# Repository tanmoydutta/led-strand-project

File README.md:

# Autonoe
An RGB and Neopixel LED controller board powered by ESP32-C3

The module has option for unified 5V supply for LEDs and the MCU LDO and can provide support for higher voltages via the dedicated barrel jack socket. Separate 5V power then can be supplied via the USB-C connector -

A small solder bridge unifies the circuit power for 5V power operations and for higher current feed via the barrel jack socket-

Dual LED interface for RGB and Addressable LEDs - 

This is an OSHWA certified hardware - 
<p align="center">
  
</p>

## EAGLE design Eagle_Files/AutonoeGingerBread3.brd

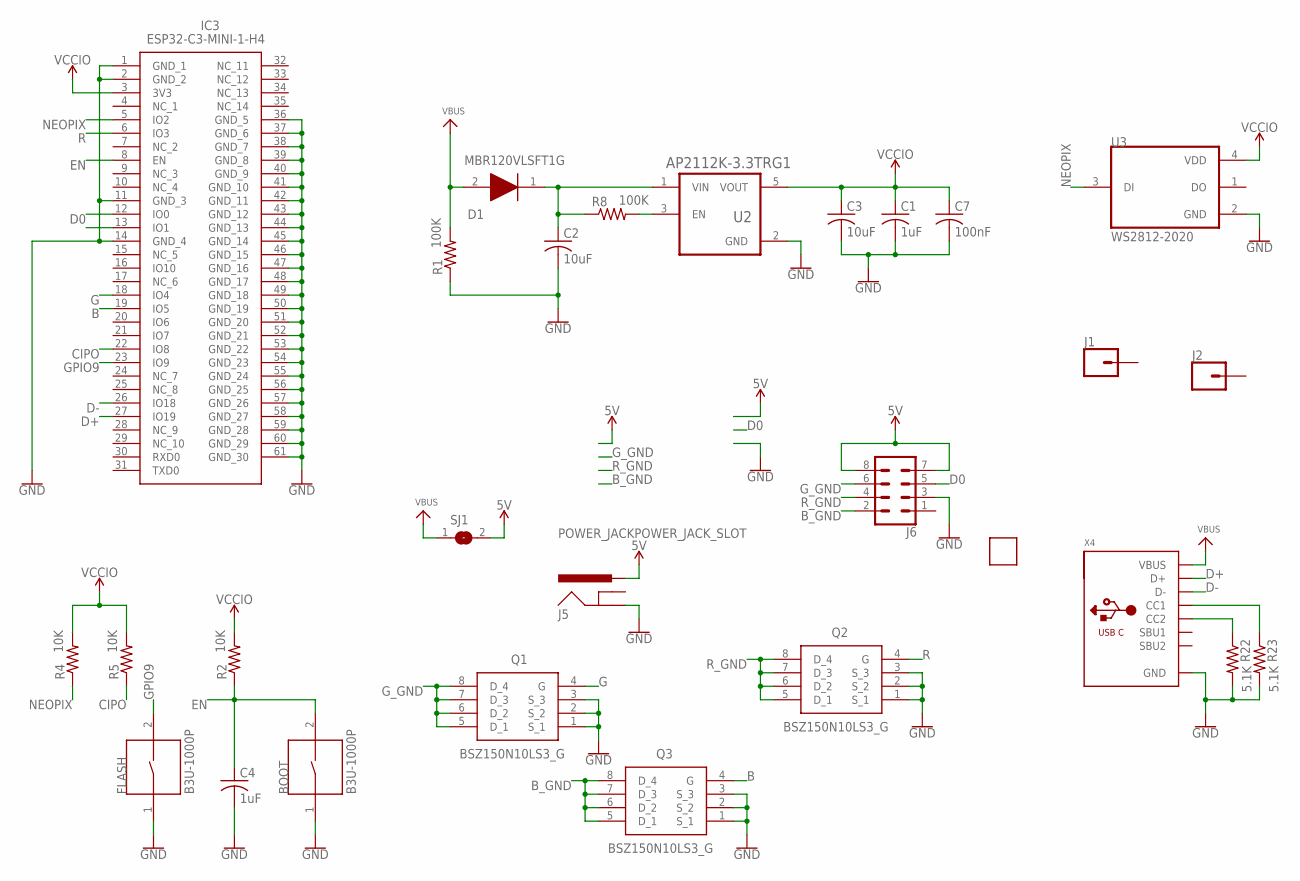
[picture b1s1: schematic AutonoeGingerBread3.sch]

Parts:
BOOT: B3U-1000P; SW_B3U-1000P
C1, C4: 1uF; C0402
C2, C3: 10uF; C0402
C7: 100nF; C0402
D1: MBR120VLSFT1G; SODFL3616X98N
FLASH: B3U-1000P; SW_B3U-1000P
IC3: ESP32-C3-MINI-1-H4; ESP32C3MINI1H4
J1, J2: CONN_01PTH_2MM; 1X01_2MM
J5: POWER_JACKPOWER_JACK_SLOT; POWER_JACK_PTH_SLOT
J6: CONN_04X2; 2X4
Q1, Q2, Q3: BSZ150N10LS3_G; BSZ180P03NS3EGATMA1
R1, R8: 100K; R0402
R2, R4, R5: 10K; R0402
R22, R23: 5.1K; R0402
SJ1: SJ
U2: AP2112K-3.3TRG1; SOT95P285X140-5N
U3: WS2812-2020; LED_WS2812-2020
U$3: SMARTT_SMALL
X4: MICROBUILDER_USB_C; MICROBUILDER_USB_C_CUSB31-CFM2AX-01-X

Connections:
5V: J5.PWR, J6.7, J6.8, SJ1.2
B: IC3.19 (IO5), Q3.4 (G)
B_GND: J6.2, Q3.5 (D_1), Q3.6 (D_2), Q3.7 (D_3), Q3.8 (D_4)
CIPO: IC3.22 (IO8), R5.1
D0: IC3.12 (IO0), J6.5
D+: IC3.27 (IO19), X4.A6 (D+), X4.B6 (D+)
D-: IC3.26 (IO18), X4.A7 (D-), X4.B7 (D-)
EN: BOOT.2, C4.1, IC3.8 (EN), R2.1
G: IC3.18 (IO4), Q1.4 (G)
GND: BOOT.1, C1.2, C2.2, C3.2, C4.2, C7.2, FLASH.1, IC3.1 (GND_1), IC3.2 (GND_2), IC3.11 (GND_3), IC3.14 (GND_4), IC3.36 (GND_5), IC3.37 (GND_6), IC3.38 (GND_7), IC3.39 (GND_8), IC3.40 (GND_9), IC3.41 (GND_10), IC3.42 (GND_11), IC3.43 (GND_12), IC3.44 (GND_13), IC3.45 (GND_14), IC3.46 (GND_15), IC3.47 (GND_16), IC3.48 (GND_17), IC3.49 (GND_18), IC3.50 (GND_19), IC3.51 (GND_20), IC3.52 (GND_21), IC3.53 (GND_22), IC3.54 (GND_23), IC3.55 (GND_24), IC3.56 (GND_25), IC3.57 (GND_26), IC3.58 (GND_27), IC3.59 (GND_28), IC3.60 (GND_29), IC3.61 (GND_30), J5.GND, J6.3, Q1.1 (S_1), Q1.2 (S_2), Q1.3 (S_3), Q2.1 (S_1), Q2.2 (S_2), Q2.3 (S_3), Q3.1 (S_1), Q3.2 (S_2), Q3.3 (S_3), R1.1, R22.2, R23.2, U2.2 (GND), U3.2 (GND), X4.A1B12 (GND), X4.B1A12 (GND)
GPIO9: FLASH.2, IC3.23 (IO9)
G_GND: J6.6, Q1.5 (D_1), Q1.6 (D_2), Q1.7 (D_3), Q1.8 (D_4)
unnamed: C2.1, D1.1 (K), R8.1, U2.1 (VIN)
unnamed: R22.1, X4.B5 (CC2)
unnamed: R23.1, X4.A5 (CC1)
unnamed: R8.2, U2.3 (EN)
NEOPIX: IC3.5 (IO2), R4.1, U3.3 (DI)
R: IC3.6 (IO3), Q2.4 (G)
R_GND: J6.4, Q2.5 (D_1), Q2.6 (D_2), Q2.7 (D_3), Q2.8 (D_4)
VBUS: D1.2 (A), R1.2, SJ1.1, X4.A4B9 (VBUS), X4.B4A9 (VBUS)
VCCIO: C1.1, C3.1, C7.1, IC3.3 (3V3), R2.2, R4.2, R5.2, U2.5 (VOUT), U3.4 (VDD)

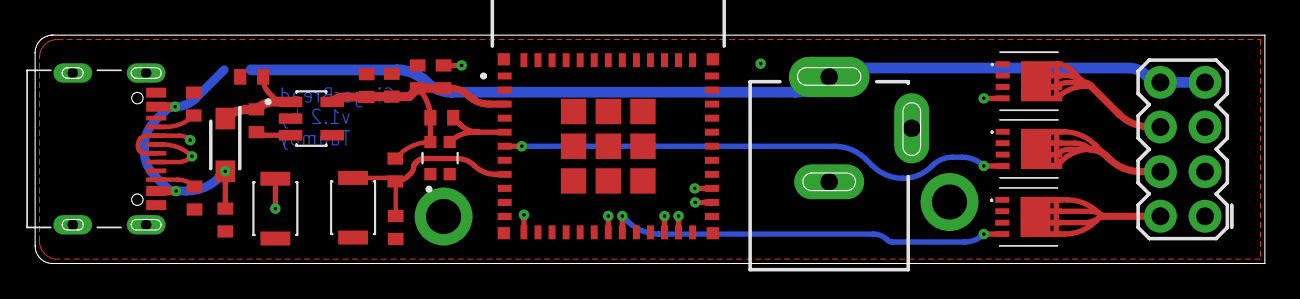
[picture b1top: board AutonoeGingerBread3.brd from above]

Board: 4 copper layers, 70.0 x 13.0 mm, 28 parts (1 on the bottom side), 21 nets.

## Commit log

2025-11-17 Adding source code
2025-11-17 Reorganising files
2025-11-17 .DS_Store banished!
2025-11-19 Adding files
2025-11-19 Add and update documentation
2025-11-19 Adding images
2025-11-19 Revise README for Autonoe LED controller project
    Updated project name and added detailed description with images.
2025-11-19 Adding documentation
2025-11-19 Add images to README for project illustration
    Added images to README for better visualization.
2025-11-19 Adjusting image
2025-11-21 Adding OSHWA certification image
2025-11-21 Update README with OSHWA certification details
    Added OSHWA certification information and logo.

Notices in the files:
parts and their libraries:
SparkFun-Connectors: Licensing: Creative Commons ShareAlike 4.0 International - https://creativecommons.org/licenses/by-sa/4.0
